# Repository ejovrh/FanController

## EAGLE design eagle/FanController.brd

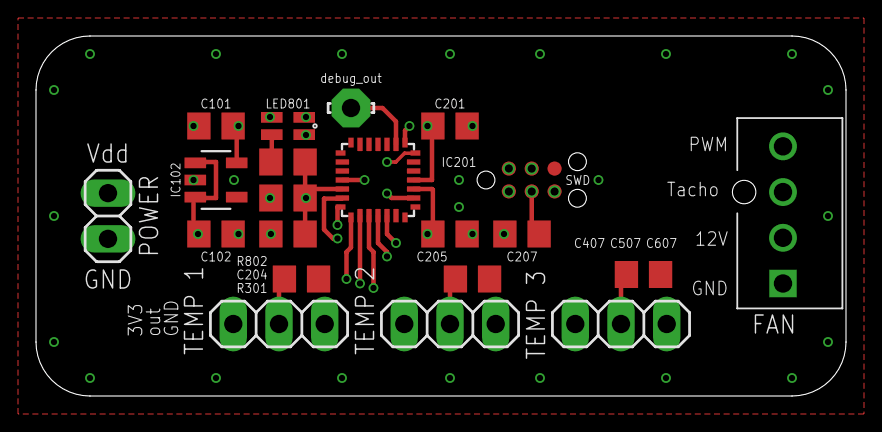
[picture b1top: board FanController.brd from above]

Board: 4 copper layers, 45.0 x 20.0 mm, 21 parts (0 on the bottom side), 15 nets.

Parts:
C101, C102: 1μF / 50V; C0805
C201, C205, C207: 0.1u; C0805
C204, C407, C507, C607: 1u; C0805
DEBUG200: LSP10
IC102: LDK320AM33R; SOT-23-5L
IC201: STM32F042G6U6; UFQFPN-28
J301: 47053-1000; 470531000
JP1: n/a; 1X02
LED801: APHBM2012SURKZGKC; SMD
R301: 10k; R0805
R802: 68R; R0805
SWD1: TC2030-NL
TEMP400, TEMP500, TEMP600: LMT86LPM; 1X03

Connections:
3V3: C101.1, C201.2, C204.2, C205.2, IC102.OUT, IC201.5_VDDA, IC201.17_VDD, IC201.18_VDDIO2, LED801.4, R301.2, R802.1, SWD1.1_TVCC, TEMP400.1, TEMP500.1, TEMP600.1
FAN_PWM: IC201.12_PA6, J301.4
FAN_TACHO: IC201.11_PA5, J301.3, R301.1
GND: C101.2, C102.2, C201.1, C204.1, C205.1, C207.1, C407.1, C507.1, C607.1, IC102.GND, IC201.16_VSS, J301.1, JP1.1, SWD1.5_GND, TEMP400.3, TEMP500.3, TEMP600.3
LED1:R_A: LED801.1, R802.2
LED_GREEN: IC201.7_PA1, LED801.3
LED_RED: IC201.6_PA0, LED801.2
STM32:DEBUG_OUT: DEBUG200.MP, IC201.23_PA15
SYS_NRST: C207.2, IC201.4_NRST, SWD1.3_T_NRST
SYS_SWCLK: IC201.22_PA14, SWD1.4_T_SWCLK
SYS_SWDIO: IC201.21_PA13, SWD1.2_T_SWDIO
TEMP1: C407.2, IC201.8_PA2, TEMP400.2
TEMP2: C507.2, IC201.9_PA3, TEMP500.2
TEMP3: C607.2, IC201.10_PA4, TEMP600.2
VDD: C102.1, IC102.EN, IC102.IN, J301.2, JP1.2

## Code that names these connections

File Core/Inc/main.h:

/* USER CODE BEGIN Header */
/**
 ******************************************************************************
 * @file           : main.h
 * @brief          : Header for main.c file.
 *                   This file contains the common defines of the application.
 ******************************************************************************
 * @attention
 *
 * Copyright (c) 2023 STMicroelectronics.
 * All rights reserved.
 *
 * This software is licensed under terms that can be found in the LICENSE file
 * in the root directory of this software component.
 * If no LICENSE file comes with this software, it is provided AS-IS.
 *
 ******************************************************************************
 */
/* USER CODE END Header */

/* Define to prevent recursive inclusion -------------------------------------*/
#ifndef __MAIN_H
#define __MAIN_H

#ifdef __cplusplus
extern "C" {
#endif

/* Includes ------------------------------------------------------------------*/
#include "stm32f0xx_hal.h"

/* Private includes ----------------------------------------------------------*/
/* USER CODE BEGIN Includes */

/* USER CODE END Includes */

/* Exported types ------------------------------------------------------------*/
/* USER CODE BEGIN ET */

/* USER CODE END ET */

/* Exported constants --------------------------------------------------------*/
/* USER CODE BEGIN EC */
enum ADCChannels
{  // order is important! - this MCU has no ranking and the order of channels is defined by channel number
	  Temp1,  // temperature sensor 1 - PA2
	  Temp2,  // temperature sensor 1 - PA3
	  Temp3,	// temperature sensor 1 - PA4
	  Tempint,  // internal temperature sensor; value in tenths of degrees Celsius
	  Vdda  // internal reference voltage
};
/* USER CODE END EC */

/* Exported macro ------------------------------------------------------------*/
/* USER CODE BEGIN EM */

/* USER CODE END EM */

void HAL_TIM_MspPostInit(TIM_HandleTypeDef *htim);

/* Exported functions prototypes ---------------------------------------------*/
void Error_Handler(void);

/* USER CODE BEGIN EFP */

/*
 * fan PWM current consumption
 * duty cycle - RPM (measured) - current/mA - tacho signal period (measured approx.)/ms
 * 		100% - 2271 RPM - 64 mA - 13.4
 * 		90% - 2082 RPM - 54 mA - 14
 * 		80% - 1875 RPM - 44 mA - 16
 * 		70% - 1665 RPM - 37 mA - 18
 * 		60% - 1428 RPM - 30 mA - 21
 * 		50% - 1200 RPM - 24 mA - 26
 * 		40% - 936 RPM - 19 mA - 32
 * 		30% - 681 RPM - 16 mA - 44
 * 		20% - 417 RPM - 13 mA - 72
 * 		10% - 179 RPM - 11 mA - 170
 * 		0% - 0 RPM - 9 mA
 */

/* USER CODE END EFP */

/* Private defines -----------------------------------------------------------*/
#define TS_CAL2 *((uint16_t*) ((uint32_t) 0x1FFFF7C2))
#define FAN_DUTY_CYCLE 0	// fan duty cycle, 0 to 100%
#define TS_CAL1 *((uint16_t*) ((uint32_t) 0x1FFFF7B8))
#define TEMPERATURE_OFFSET -35	// correction value (offset) for temperature calculation
#define VREFINT_CAL *((uint16_t*) ((uint32_t) 0x1FFFF7BA))
#define ADC_CHANNELS 5 // 3 external (IN2,3,4) and one internal temperature channels, Vrefint
#define TIMER1_PERIOD 124 // ADC trigger timer
#define ADC_MEASURE_ITERATIONS 80 // measure timer1 period times this number == 1s
#define TIMER2_PERIOD 0xFFFFFFFF // PA5 - fan tacho
#define TIMER3_PERIOD 99 // PA6 - fan PWM
#define TIMER_PRESCALER 799
#define TACHO_BUFFER_LEN 10 // size of ADC readout buffer
#define USE_DEBUG_PIN 0 // make use of PA15
#define USE_SLEEP 1 // enter sleep mode once an ISR is finished
#define LED_RED_Pin GPIO_PIN_0
#define LED_RED_GPIO_Port GPIOA
#define LED_GREEN_Pin GPIO_PIN_1
#define LED_GREEN_GPIO_Port GPIOA
#define TEMP1_SIGNAL_Pin GPIO_PIN_2
#define TEMP1_SIGNAL_GPIO_Port GPIOA
#define TEMP2_SIGNAL_Pin GPIO_PIN_3
#define TEMP2_SIGNAL_GPIO_Port GPIOA
#define TEMP3_SIGNAL_Pin GPIO_PIN_4
#define TEMP3_SIGNAL_GPIO_Port GPIOA
#define FAN_TACHO_Pin GPIO_PIN_5
#define FAN_TACHO_GPIO_Port GPIOA
#define FAN_PWM_Pin GPIO_PIN_6
#define FAN_PWM_GPIO_Port GPIOA
#define debug_out_Pin GPIO_PIN_15
#define debug_out_GPIO_Port GPIOA

/* USER CODE BEGIN Private defines */

/* USER CODE END Private defines */

#ifdef __cplusplus
}
#endif

#endif /* __MAIN_H */

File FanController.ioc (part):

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Mcu.Name=STM32F042G(4-6)Ux
Mcu.Package=UFQFPN28
Mcu.UserName=STM32F042G6Ux
PA0.GPIOParameters=PinState,GPIO_Label
PA0.GPIO_Label=LED_RED
PA0.PinState=GPIO_PIN_SET
PA0.Signal=GPIO_Output
PA1.GPIOParameters=PinState,GPIO_Label
PA1.GPIO_Label=LED_GREEN
PA1.PinState=GPIO_PIN_SET
PA1.Signal=GPIO_Output
PA13.Mode=Serial_Wire
PA13.Signal=SYS_SWDIO
PA14.Mode=Serial_Wire
PA14.Signal=SYS_SWCLK
PA15.GPIOParameters=GPIO_Label
PA15.GPIO_Label=debug_out
PA15.Signal=GPIO_Output
PA2.GPIOParameters=GPIO_Label
PA2.GPIO_Label=TEMP1_SIGNAL
PA2.Mode=IN2
PA2.Signal=ADC_IN2
PA3.GPIOParameters=GPIO_Label
PA3.GPIO_Label=TEMP2_SIGNAL
PA3.Mode=IN3
PA3.Signal=ADC_IN3
PA4.GPIOParameters=GPIO_Label
PA4.GPIO_Label=TEMP3_SIGNAL
PA4.Mode=IN4
PA4.Signal=ADC_IN4
PA5.GPIOParameters=GPIO_Label
PA5.GPIO_Label=FAN_TACHO
PA5.Signal=S_TIM2_CH1_ETR
PA6.GPIOParameters=GPIO_Label
PA6.GPIO_Label=FAN_PWM
PA6.Signal=S_TIM3_CH1
RCC.SYSCLKFreq_VALUE=8000000
board=custom

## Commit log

2023-03-15 initial commit of a quick and dirty fan controller design
2023-05-04 rev. 2 board: - sized up vias for SWD to 0.45mm
2023-05-06 - removed 2V5 voltage reference since it is useless
2023-05-14 - modified .gitignore to exclude eagle temporary files and debug/build stuff
2023-05-14 - updated .gitignore again
2023-05-14 - added DMA to ADC and input capture timer2
2023-05-14 - timer3 PWM signal (fan) generation works
2023-05-14 - got timer2/DMA-based ADC to work - tiemr3 tacho is showing signs of some life; needs more work
2023-05-14 - implemented ADC average calculation in ISR
2023-09-14 - commit before rev.2 rev.2 is switch to PWM fans
2023-09-16 rev.2: PWM fan
    - initialized all unused pins as analog
    - replaced 3-pin fan connector with 4-pin
    - removed FET for transistor control
    - added noctua PWM specification white paper
    - rev.2 board marking on tstop
2023-09-16 - replaced fan connector with pinhead (fan will be soldered)
2023-09-16 rev.2: PWM fan a PWM fan shall be connected to the controller
    - initialized all unused pins as analog
    - removed FET for transistor control
    - added noctua PWM specification white paper
    - rev.2 board marking on tstop
    - replaced connectors with pin headers
2023-09-16 - small routing correction
2023-10-10 - coded ADC temperature calculations (timer1) - coded RPM calculations (timer2)
2023-10-10 - converted to 4 layer board and sent to FAB - coded ADC temperature calculations (timer1) - coded RPM calculations (timer2)

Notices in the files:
parts and their libraries:
tag-connect: ©2009 ROFA.cz - modified and updated by Robert Darlington ‹rdarlington@gmail.com›
